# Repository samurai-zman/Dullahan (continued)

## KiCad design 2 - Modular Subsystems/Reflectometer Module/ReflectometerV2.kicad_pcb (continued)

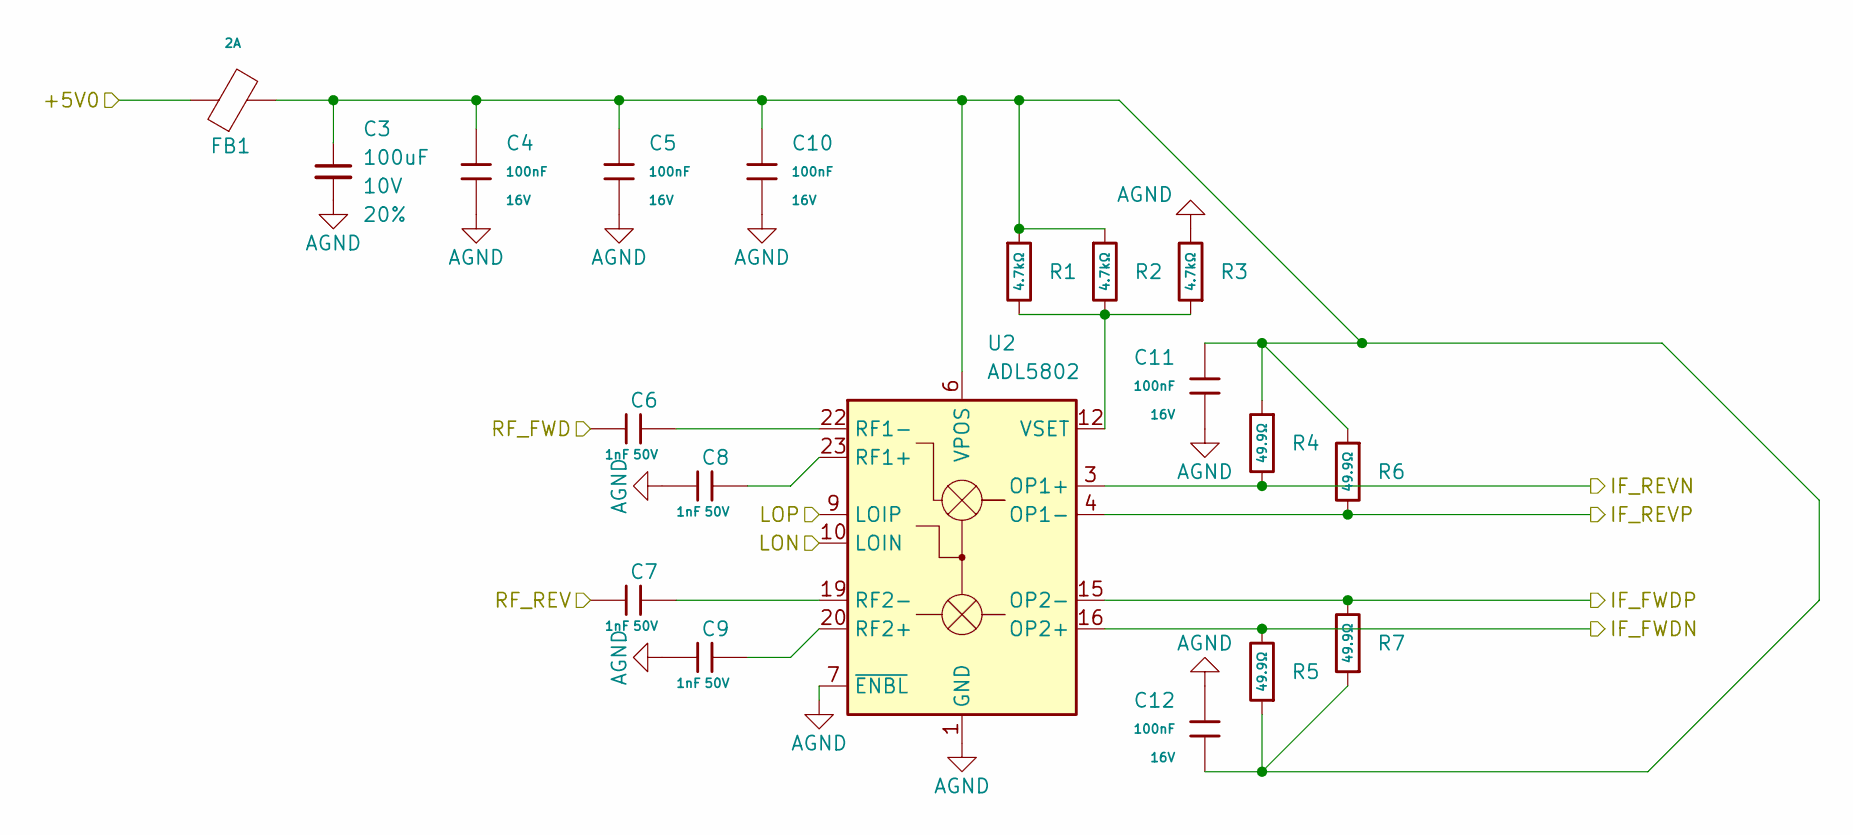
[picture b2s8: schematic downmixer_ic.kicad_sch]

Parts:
C3: 100uF; C_0402_1005Metric; Voltage 10V; Tolerance 20%
C4, C5, C10, C11, C12: 100nF; C_0402; Voltage Rated 16V; Tolerance ±10%; Part CL05B104KO5NNNC; LCSC C1525
C6, C7, C8, C9: 1nF; C_0402; Voltage Rated 50V; Tolerance ±10%; Part 0402B102K500NT; LCSC C1523
FB1: FB_0603; Current Rating 2A; Tolerance ±25%; Part BLM18PG121SN1D; LCSC C14709
R1, R2, R3: 4.7kΩ; R_0402; Overload Voltage (Max) 50V; Tolerance ±1%; Part 0402WGF4701TCE; LCSC C25900
R4, R5, R6, R7: 49.9Ω; R_0402; Overload Voltage (Max) 50V; Tolerance ±1%; Part 0402WGF499JTCE; LCSC C25120
U2: ADL5802; LFCSP-24-1EP_4x4mm_P0.5mm_EP2.5x2.5mm

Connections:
/DE Amplifier/RFin1N: R5.2, U2.16 (OP2+); also elsewhere on the board
/DE Amplifier/RFin1P: R7.2, U2.15 (OP2-); also elsewhere on the board
/DE Amplifier/RFin2N: R4.2, U2.3 (OP1+); also elsewhere on the board
/DE Amplifier/RFin2P: R6.2, U2.4 (OP1-); also elsewhere on the board
/DOWNMIXER/LON: U2.10 (LOIN); also elsewhere on the board
/DOWNMIXER/LOP: U2.9 (LOIP); also elsewhere on the board
/DOWNMIXER/RF_FWD: C6.1; also elsewhere on the board
/DOWNMIXER/RF_REV: C7.1; also elsewhere on the board
AGND: C3.2, C4.1, C5.1, C8.1, C9.1, C10.1, C11.1, C12.2, R3.2, U2.1 (GND), U2.2 (GND), U2.5 (GND), U2.7 (~ENBL), U2.8 (GND), U2.11 (GND), U2.14 (GND), U2.17 (GND), U2.18 (GND), U2.21 (GND), U2.25 (GND); also elsewhere on the board
unnamed: C3.1, C4.2, C5.2, C10.2, C11.2, C12.1, FB1.2, R1.1, R2.1, R4.1, R5.1, R6.1, R7.1, U2.6 (VPOS), U2.13 (VPOS), U2.24 (VPOS)
unnamed: C8.2, U2.23 (RF1+)
unnamed: C6.2, U2.22 (RF1-)
unnamed: C9.2, U2.20 (RF2+)
unnamed: C7.2, U2.19 (RF2-)
unnamed: R1.2, R2.2, R3.1, U2.12 (VSET)

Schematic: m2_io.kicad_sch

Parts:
D1: +1V8_OK; LED_1206
D2: +3V3_OK; LED_1206
D3: +5V0_OK; LED_1206
J2: Bus_M.2_Socket_M; M.2_22110-xx-M
J4: Conn_01x04; PinSocket_1x04_P2.54mm_Vertical
R46: 60Ω; R_1206; Overload Voltage (Max) 200V; Tolerance ±1%; Part 1206W4F1000T5E; LCSC C17901
R47: 165Ω; R_1206; Overload Voltage (Max) 200V; Tolerance ±1%; Part 1206W4F1000T5E; LCSC C17901
R48: 250Ω; R_1206; Overload Voltage (Max) 200V; Tolerance ±1%; Part 1206W4F1000T5E; LCSC C17901

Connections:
/ADC/D0: J2.56; also elsewhere on the board
/ADC/D1: J2.54; also elsewhere on the board
/ADC/D2: J2.52; also elsewhere on the board
/ADC/D3: J2.50; also elsewhere on the board
/ADC/D4: J2.48; also elsewhere on the board
/ADC/D5: J2.46; also elsewhere on the board
/ADC/D6: J2.44; also elsewhere on the board
/ADC/D7: J2.42; also elsewhere on the board
/ADC/D8: J2.40; also elsewhere on the board
/ADC/D9: J2.38; also elsewhere on the board
/ADC/D10: J2.36; also elsewhere on the board
/ADC/D11: J2.34; also elsewhere on the board
/ADC/OTR_A: J2.32; also elsewhere on the board
/ADC/OTR_B: J2.30; also elsewhere on the board
/Clock/CLK_READ: J2.55; also elsewhere on the board
/DAC/DAC_CTRL0: J2.16; also elsewhere on the board
/DAC/DAC_CTRL1: J2.20, J4.2; also elsewhere on the board
/DAC/DAC_CTRL2: J2.14; also elsewhere on the board
/DAC/DAC_CTRL3: J2.24, J4.4; also elsewhere on the board
/DAC/DAC_CTRL4: J2.22, J4.3; also elsewhere on the board
/DAC/DAC_CTRL5: J2.18, J4.1; also elsewhere on the board
/DE Amplifier/DITHER: J2.26; also elsewhere on the board
/M2 Connector/PLL_CTRL2: J2.10; also elsewhere on the board
/M2 Connector/PLL_CTRL3: J2.6; also elsewhere on the board
/M2 Connector/PLL_CTRL4: J2.8; also elsewhere on the board
AGND: J2.1, J2.2, J2.3, J2.4, J2.5, J2.7, J2.9, J2.11, J2.12, J2.13, J2.15, J2.17, J2.19, J2.21, J2.23, J2.25, J2.27, J2.28, J2.29, J2.31, J2.33, J2.35, J2.37, J2.39, J2.41, J2.43, J2.45, J2.47, J2.49, J2.51, J2.53, J2.57, J2.58, J2.67, J2.74, J2.75, J2.S1 (SHIELD), J2.S2 (SHIELD__1), R46.2, R47.2, R48.2; also elsewhere on the board
unnamed: D1.1 (K), R46.1
unnamed: D2.1 (K), R47.1
unnamed: D3.1 (K), R48.1

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
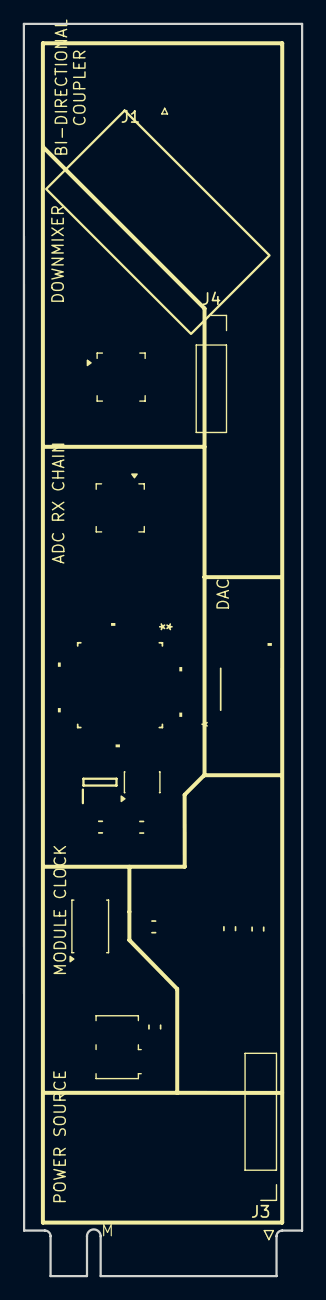
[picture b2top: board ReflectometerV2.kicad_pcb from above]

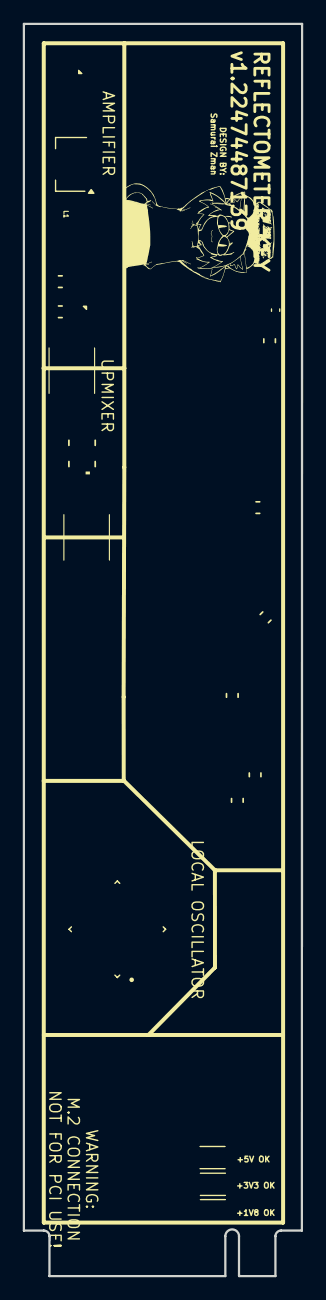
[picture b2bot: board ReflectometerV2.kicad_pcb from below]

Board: 6 copper layers, 24.4 x 110.0 mm, 203 parts (100 on the bottom side), 148 nets.

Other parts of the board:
C13, C15: 10uF; C_0402
C14, C18, C90, C91, C92, C93, C94, C99: 1nF; C_0402
C16, C17: 100nF; C_0402
C95: 10nF; C_0402
C96: 2.2uF; C_0402
C97, C98: 1.2pF; C_0402
FB2, FB3: FB_0603
L1: LQW15CA1R0K00D; INDC1005X66N
R8, R9, R10: 10Ω; R_0402
R11: 16.5Ω; R_0402
T1, T2: PL-395
U3: PAT1220-C-6DB; RF_Attenuator_Susumu_PAT1220
U4: GVA-93+; SOT-89-3
U5: PAT1220-C-10DB; RF_Attenuator_Susumu_PAT1220
U10: LTC5562IUC-TRPBF; 05-08-1534_ADI

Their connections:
/DAC/IF_OUT: C90.1; also elsewhere on the board
/PLL/RFoutAN: C94.1; also elsewhere on the board
/PLL/RFoutAP: C93.1; also elsewhere on the board
/SE Amplifier/RF Input: C99.1, U3.1
/SE Amplifier/RF Output: U5.2; also elsewhere on the board
/UPMIXER/LO_N: C94.2, U10.2 (LO-)
/UPMIXER/LO_P: C93.2, U10.1 (LO+)
AGND: C13.1, C15.1, C16.1, C17.1, C95.1, C96.2, R9.1, T1.1 (GND), T1.2 (GND), T2.1 (GND), T2.2 (GND), U3.3, U4.2 (GND_2), U5.3, U10.7 (GND), U10.10 (LGND), U10.11 (GND); also elsewhere on the board
unnamed: C13.2, FB2.2, FB3.1
unnamed: C14.1, R10.2
unnamed: C14.2, U4.1
unnamed: C15.2, C16.2, FB3.2, R11.2
unnamed: C17.2, L1.2, R11.1
unnamed: C18.1, L1.1, U4.3
unnamed: C18.2, U5.1
unnamed: R8.1, U3.2
unnamed: R8.2, R9.2, R10.1
unnamed: C92.1, T1.4 (DEN)
unnamed: C91.1, T1.5 (DEP)
unnamed: C90.2, T1.3 (SE)
unnamed: C97.2, T2.4 (DEN)
unnamed: C98.2, T2.5 (DEP)
unnamed: C99.2, T2.3 (SE)
unnamed: C91.2, U10.9 (IN+)
unnamed: C92.2, U10.8 (IN-)
unnamed: C97.1, U10.4 (OUT+)
unnamed: C98.1, U10.5 (OUT-)
